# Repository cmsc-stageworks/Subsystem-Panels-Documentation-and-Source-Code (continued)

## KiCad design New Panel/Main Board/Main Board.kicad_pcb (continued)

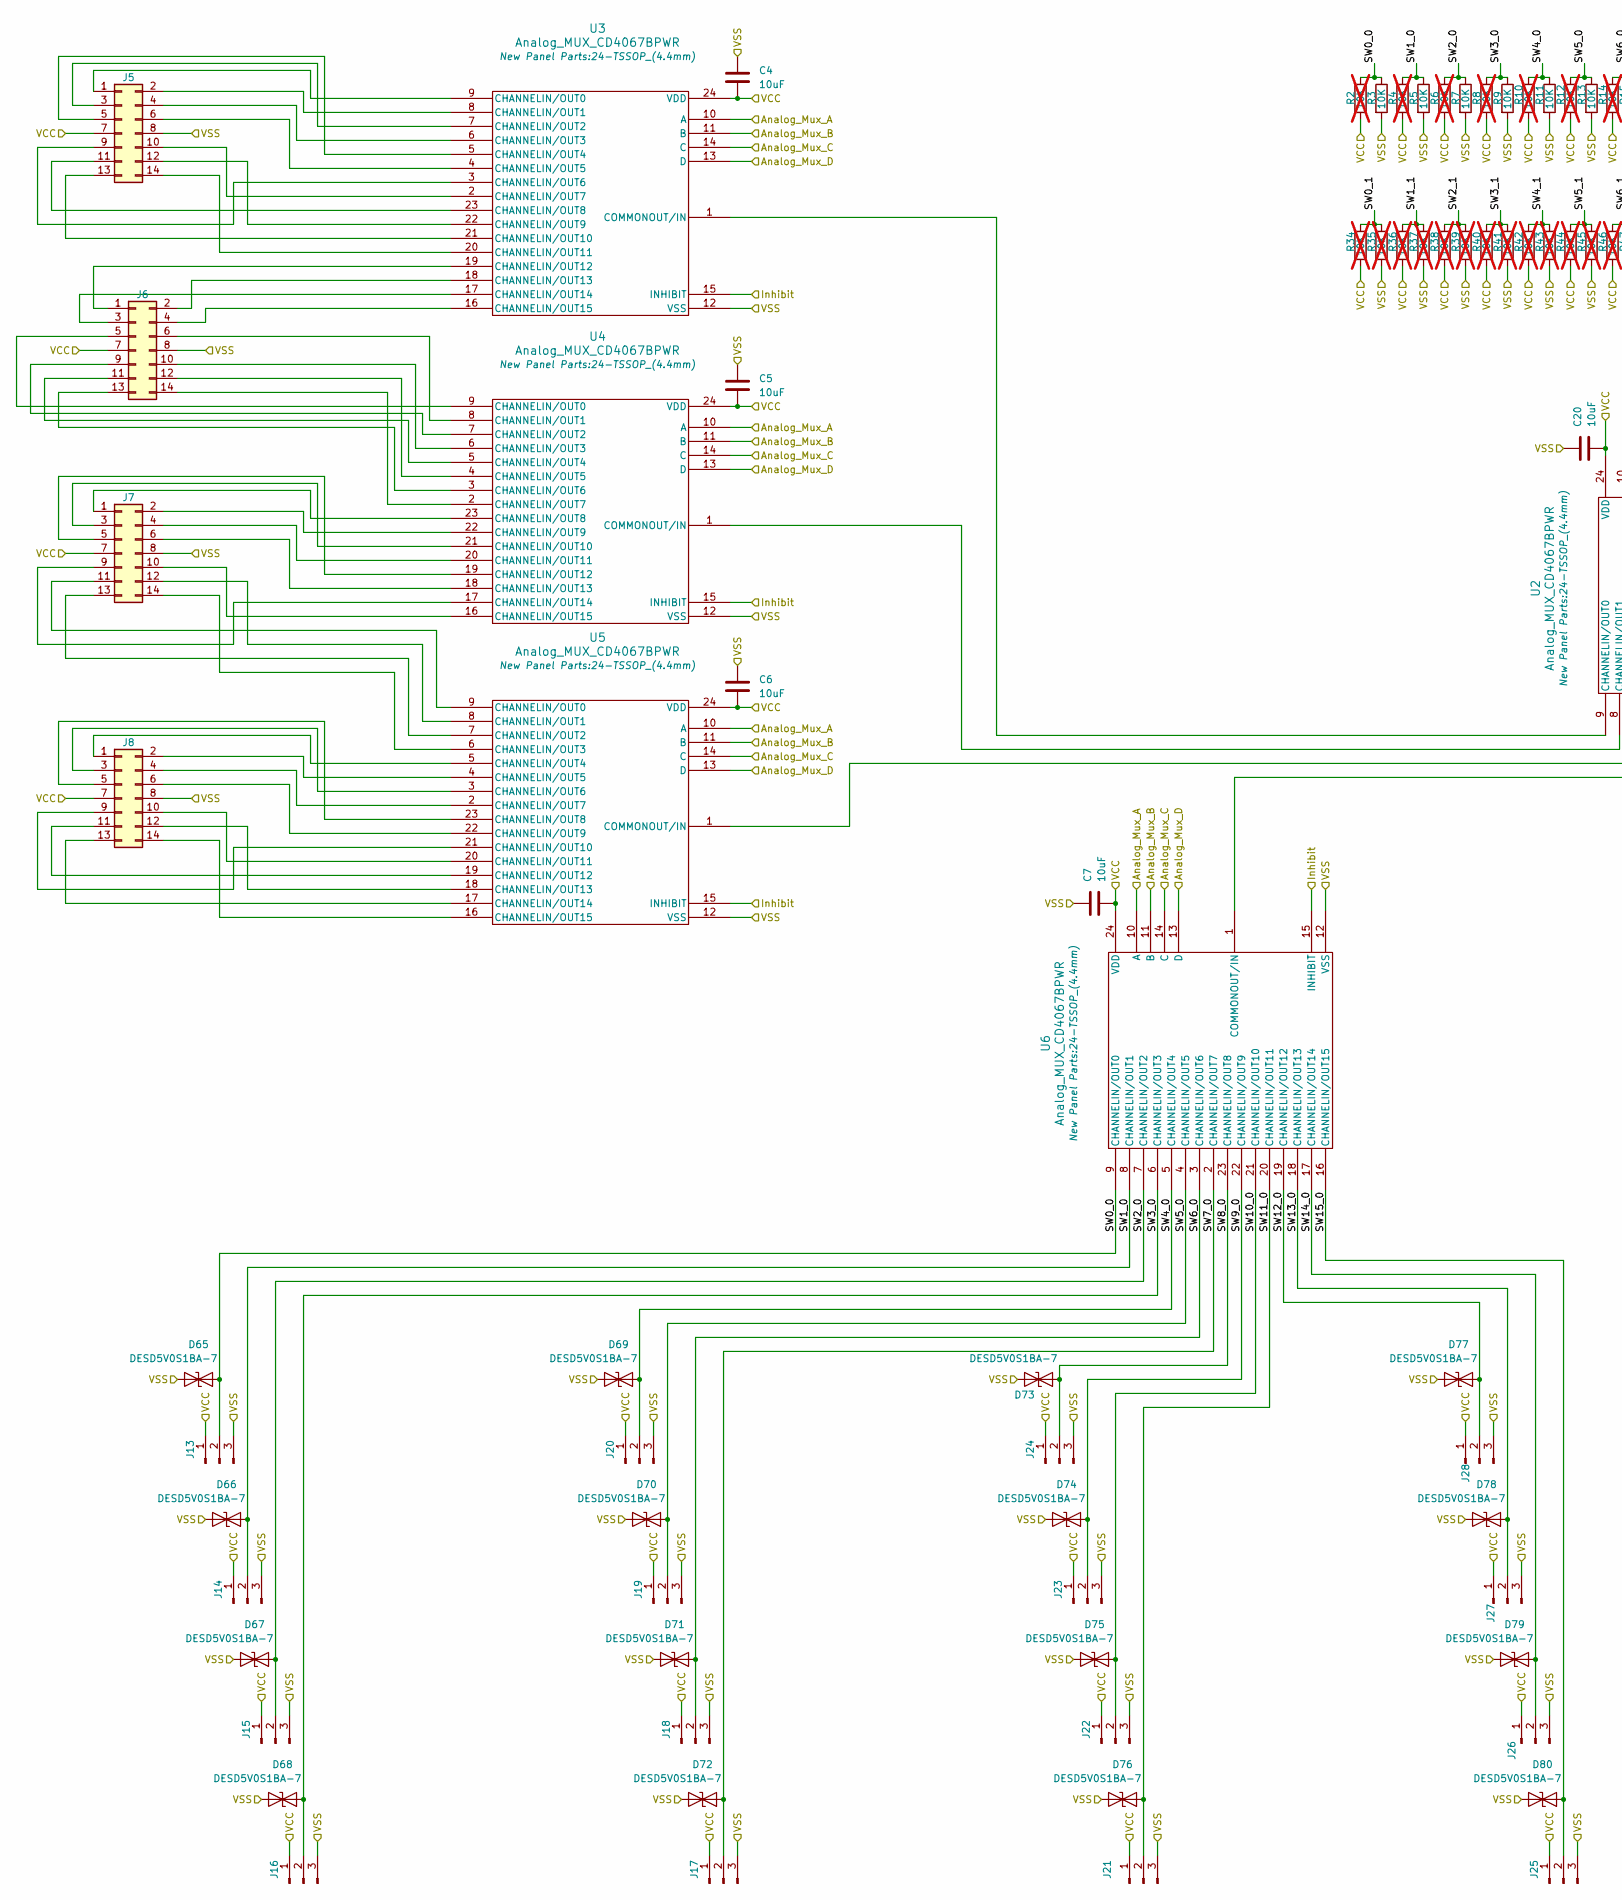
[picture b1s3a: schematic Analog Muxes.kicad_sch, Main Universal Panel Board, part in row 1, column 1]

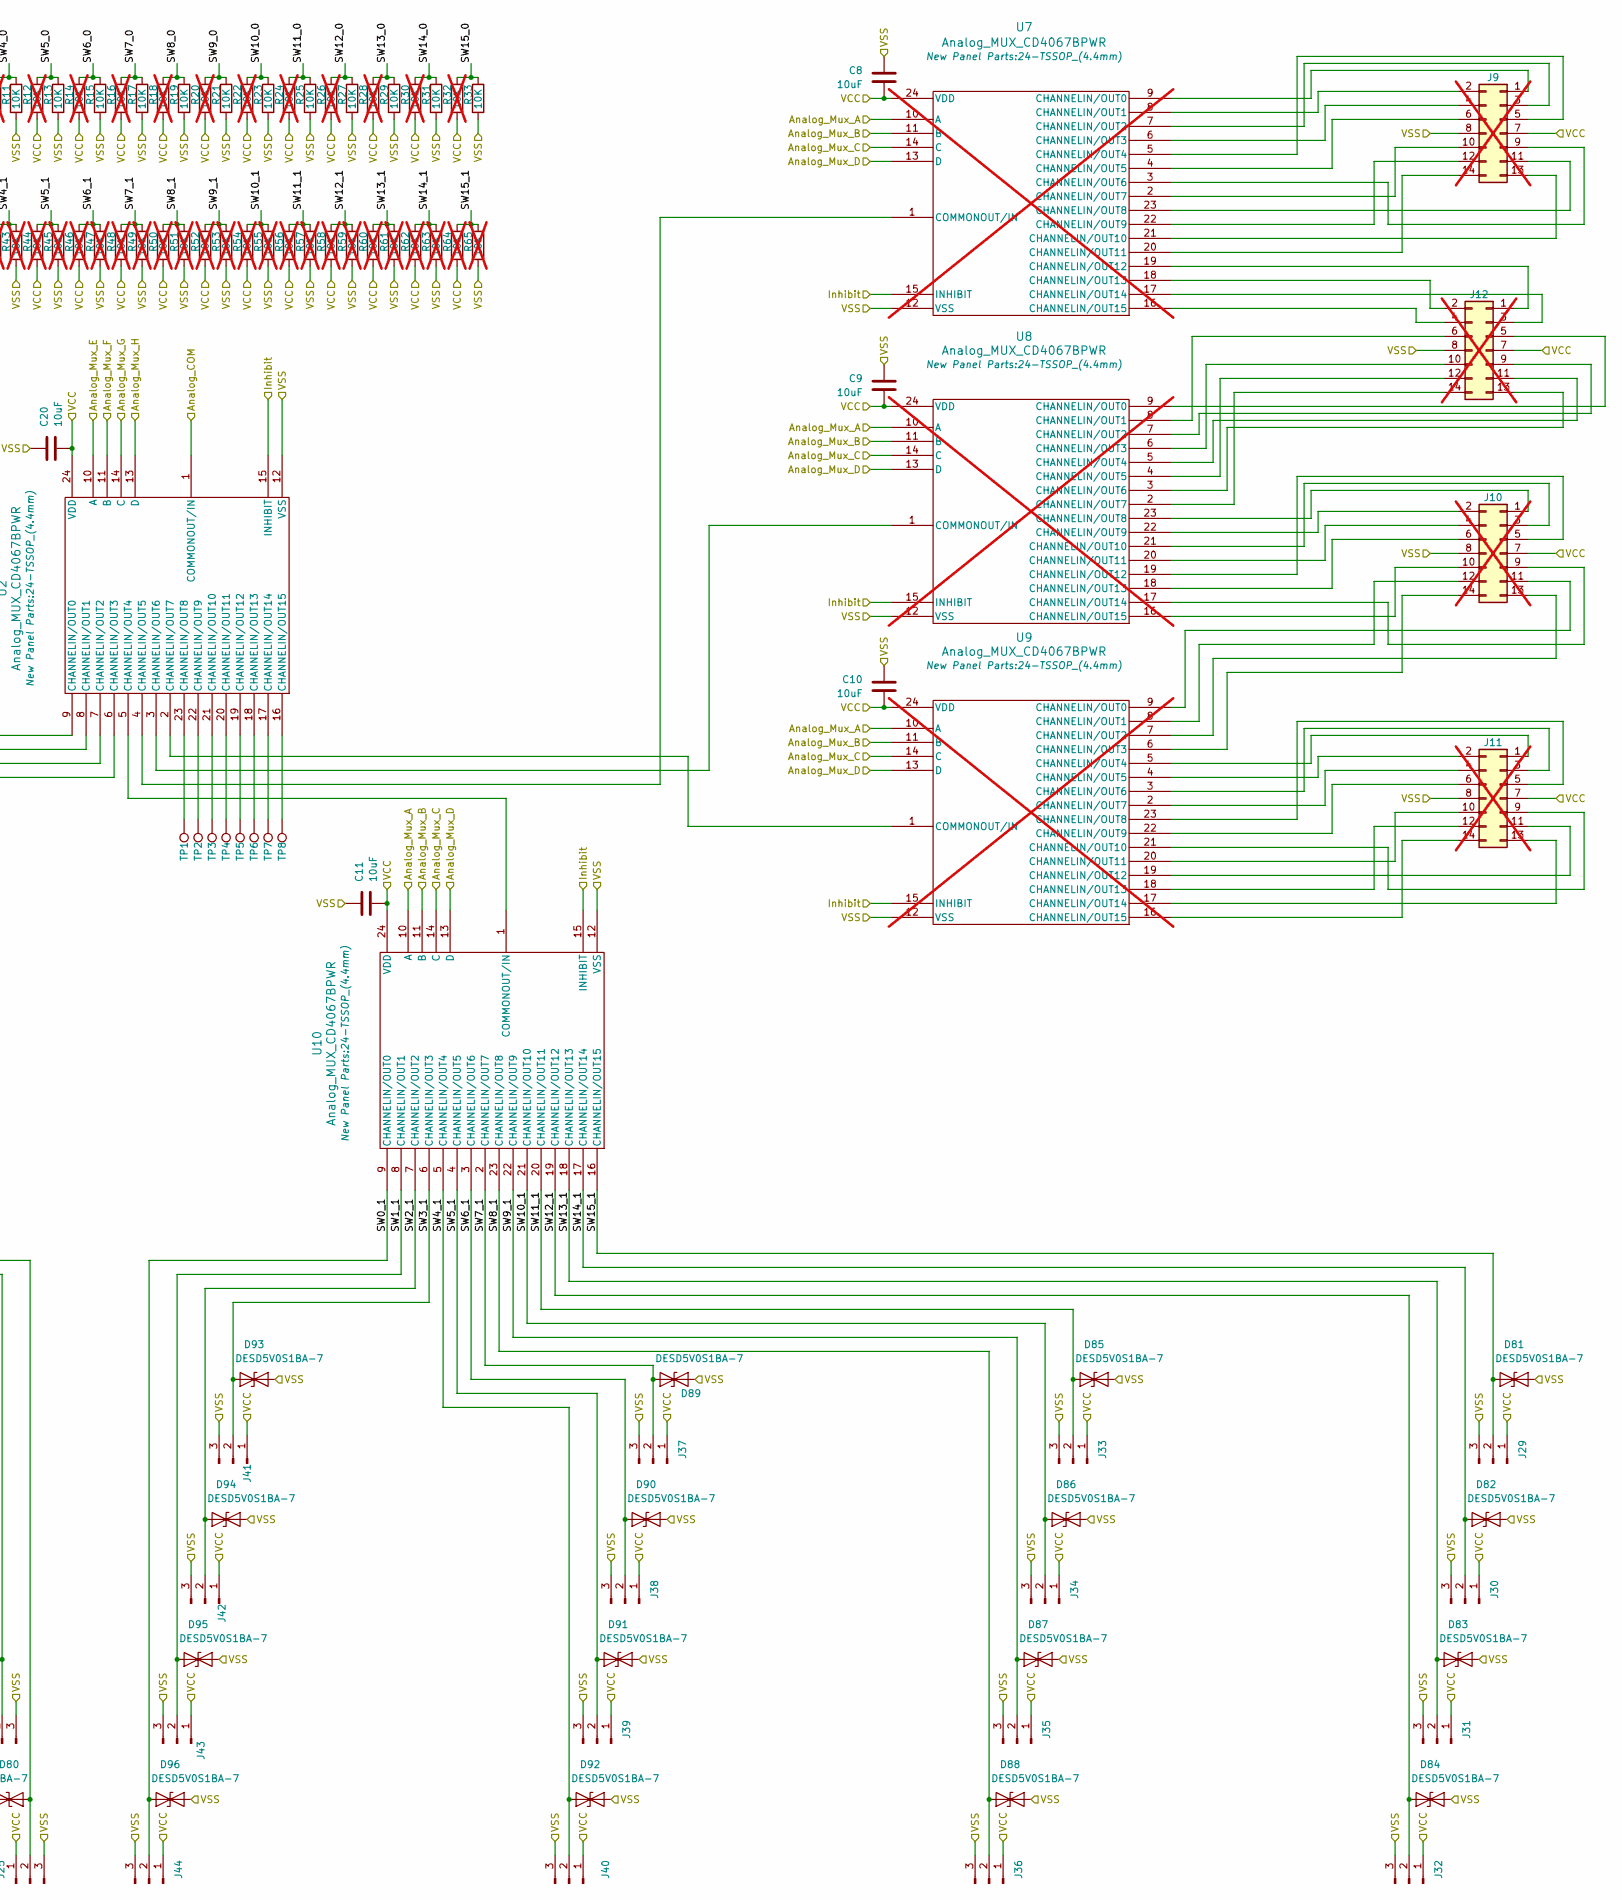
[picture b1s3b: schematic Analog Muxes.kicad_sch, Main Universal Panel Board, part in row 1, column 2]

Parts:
C4, C5, C6, C7, C8, C9, C10, C11, C20: 10uF; C_0603_1608Metric_Pad1.08x0.95mm_HandSolder
D65, D66, D67, D68, D69, D70, D71, D72, D73, D74, D75, D76, D77, D78, D79, D80, D81, D82, D83, D84, D85, D86, D87, D88, D89, D90, D91, D92, D93, D94, D95, D96: DESD5V0S1BA-7; D_SOD-323
J5, J6, J7, J8: Conn_02x07_Odd_Even; IDC-Header_2x07_P2.54mm_Vertical
J9, J10, J11, J12: Conn_02x07_Odd_Even; IDC-Header_2x07_P2.54mm_Vertical; not fitted
J13, J14, J15, J16, J17, J18, J19, J20, J21, J22, J23, J24, J25, J26, J27, J28, J29, J30, J31, J32, J33, J34, J35, J36, J37, J38, J39, J40, J41, J42, J43, J44: Conn_01x03_Pin; JST_PH_B3B-PH-K_1x03_P2.00mm_Vertical
R2, R4, R6, R8, R10, R12, R14, R16, R18, R20, R22, R24, R26, R28, R30, R32, R34, R35, R36, R37, R38, R39, R40, R41, R42, R43, R44, R45, R46, R47, R48, R49, R50, R51, R52, R53, R54, R55, R56, R57, R58, R59, R60, R61, R62, R63, R64, R65: 10K; R_0603_1608Metric; not fitted
R3, R5, R7, R9, R11, R13, R15, R17, R19, R21, R23, R25, R27, R29, R31, R33: 10K; R_0603_1608Metric
TP1, TP2, TP3, TP4, TP5, TP6, TP7, TP8: TestPoint; Pin_D1.0mm_L10.0mm
U2, U3, U4, U5, U6, U10: Analog_MUX_CD4067BPWR; 24-TSSOP_(4.4mm); Manufacturer Part Number CD4067BPWR
U7, U8, U9: Analog_MUX_CD4067BPWR; 24-TSSOP_(4.4mm); Manufacturer Part Number CD4067BPWR; not fitted

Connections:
+3.3V: C4.2, C5.2, C6.2, C7.2, C8.2, C9.2, C10.2, C11.2, C20.2, J5.7, J6.7, J7.7, J8.7, J9.7, J10.7, J11.7, J12.7, J13.1, J14.1, J15.1, J16.1, J17.1, J18.1, J19.1, J20.1, J21.1, J22.1, J23.1, J24.1, J25.1, J26.1, J27.1, J28.1, J29.1, J30.1, J31.1, J32.1, J33.1, J34.1, J35.1, J36.1, J37.1, J38.1, J39.1, J40.1, J41.1, J42.1, J43.1, J44.1, R2.2, R4.2, R6.2, R8.2, R10.2, R12.2, R14.2, R16.2, R18.2, R20.2, R22.2, R24.2, R26.2, R28.2, R30.2, R32.2, R34.2, R36.2, R38.2, R40.2, R42.2, R44.2, R46.2, R48.2, R50.2, R52.2, R54.2, R56.2, R58.2, R60.2, R62.2, R64.2, U2.24 (VDD), U3.24 (VDD), U4.24 (VDD), U5.24 (VDD), U6.24 (VDD), U7.24 (VDD), U8.24 (VDD), U9.24 (VDD), U10.24 (VDD); also elsewhere on the board
/Analog Input Mux/Analog_COM: U2.1 (COMMONOUT/IN); also elsewhere on the board
/Analog Input Mux/Analog_Mux_A: U3.10 (A), U4.10 (A), U5.10 (A), U6.10 (A), U7.10 (A), U8.10 (A), U9.10 (A), U10.10 (A); also elsewhere on the board
/Analog Input Mux/Analog_Mux_B: U3.11 (B), U4.11 (B), U5.11 (B), U6.11 (B), U7.11 (B), U8.11 (B), U9.11 (B), U10.11 (B); also elsewhere on the board
/Analog Input Mux/Analog_Mux_C: U3.14 (C), U4.14 (C), U5.14 (C), U6.14 (C), U7.14 (C), U8.14 (C), U9.14 (C), U10.14 (C); also elsewhere on the board
/Analog Input Mux/Analog_Mux_D: U3.13 (D), U4.13 (D), U5.13 (D), U6.13 (D), U7.13 (D), U8.13 (D), U9.13 (D), U10.13 (D); also elsewhere on the board
/Analog Input Mux/Analog_Mux_E: U2.10 (A); also elsewhere on the board
/Analog Input Mux/Analog_Mux_F: U2.11 (B); also elsewhere on the board
/Analog Input Mux/Analog_Mux_G: U2.14 (C); also elsewhere on the board
/Analog Input Mux/Analog_Mux_H: U2.13 (D); also elsewhere on the board
/Analog Input Mux/Inhibit: U2.15 (INHIBIT), U3.15 (INHIBIT), U4.15 (INHIBIT), U5.15 (INHIBIT), U6.15 (INHIBIT), U7.15 (INHIBIT), U8.15 (INHIBIT), U9.15 (INHIBIT), U10.15 (INHIBIT); also elsewhere on the board
/Analog Input Mux/SW0_0: D65.1 (A1), J13.2, R2.1, R3.1, U6.9 (CHANNELIN/OUT0)
/Analog Input Mux/SW0_1: D96.1 (A1), J44.2, R34.1, R35.1, U10.9 (CHANNELIN/OUT0)
/Analog Input Mux/SW1_0: D66.1 (A1), J14.2, R4.1, R5.1, U6.8 (CHANNELIN/OUT1)
/Analog Input Mux/SW1_1: D95.1 (A1), J43.2, R36.1, R37.1, U10.8 (CHANNELIN/OUT1)
/Analog Input Mux/SW2_0: D67.1 (A1), J15.2, R6.1, R7.1, U6.7 (CHANNELIN/OUT2)
/Analog Input Mux/SW2_1: D94.1 (A1), J42.2, R38.1, R39.1, U10.7 (CHANNELIN/OUT2)
/Analog Input Mux/SW3_0: D68.1 (A1), J16.2, R8.1, R9.1, U6.6 (CHANNELIN/OUT3)
/Analog Input Mux/SW3_1: D93.1 (A1), J41.2, R40.1, R41.1, U10.6 (CHANNELIN/OUT3)
/Analog Input Mux/SW4_0: D69.1 (A1), J20.2, R10.1, R11.1, U6.5 (CHANNELIN/OUT4)
/Analog Input Mux/SW4_1: D92.1 (A1), J40.2, R42.1, R43.1, U10.5 (CHANNELIN/OUT4)
/Analog Input Mux/SW5_0: D70.1 (A1), J19.2, R12.1, R13.1, U6.4 (CHANNELIN/OUT5)
/Analog Input Mux/SW5_1: D91.1 (A1), J39.2, R44.1, R45.1, U10.4 (CHANNELIN/OUT5)
/Analog Input Mux/SW6_0: D71.1 (A1), J18.2, R14.1, R15.1, U6.3 (CHANNELIN/OUT6)
/Analog Input Mux/SW6_1: D90.1 (A1), J38.2, R46.1, R47.1, U10.3 (CHANNELIN/OUT6)
/Analog Input Mux/SW7_0: D72.1 (A1), J17.2, R16.1, R17.1, U6.2 (CHANNELIN/OUT7)
/Analog Input Mux/SW7_1: D89.1 (A1), J37.2, R48.1, R49.1, U10.2 (CHANNELIN/OUT7)
/Analog Input Mux/SW8_0: D73.1 (A1), J24.2, R18.1, R19.1, U6.23 (CHANNELIN/OUT8)
/Analog Input Mux/SW8_1: D88.1 (A1), J36.2, R50.1, R51.1, U10.23 (CHANNELIN/OUT8)
/Analog Input Mux/SW9_0: D74.1 (A1), J23.2, R20.1, R21.1, U6.22 (CHANNELIN/OUT9)
/Analog Input Mux/SW9_1: D87.1 (A1), J35.2, R52.1, R53.1, U10.22 (CHANNELIN/OUT9)
/Analog Input Mux/SW10_0: D75.1 (A1), J22.2, R22.1, R23.1, U6.21 (CHANNELIN/OUT10)
/Analog Input Mux/SW10_1: D86.1 (A1), J34.2, R54.1, R55.1, U10.21 (CHANNELIN/OUT10)
/Analog Input Mux/SW11_0: D76.1 (A1), J21.2, R24.1, R25.1, U6.20 (CHANNELIN/OUT11)
/Analog Input Mux/SW11_1: D85.1 (A1), J33.2, R56.1, R57.1, U10.20 (CHANNELIN/OUT11)
/Analog Input Mux/SW12_0: D77.1 (A1), J28.2, R26.1, R27.1, U6.19 (CHANNELIN/OUT12)
/Analog Input Mux/SW12_1: D84.1 (A1), J32.2, R58.1, R59.1, U10.19 (CHANNELIN/OUT12)
/Analog Input Mux/SW13_0: D78.1 (A1), J27.2, R28.1, R29.1, U6.18 (CHANNELIN/OUT13)
/Analog Input Mux/SW13_1: D83.1 (A1), J31.2, R60.1, R61.1, U10.18 (CHANNELIN/OUT13)
/Analog Input Mux/SW14_0: D79.1 (A1), J26.2, R30.1, R31.1, U6.17 (CHANNELIN/OUT14)
/Analog Input Mux/SW14_1: D82.1 (A1), J30.2, R62.1, R63.1, U10.17 (CHANNELIN/OUT14)
/Analog Input Mux/SW15_0: D80.1 (A1), J25.2, R32.1, R33.1, U6.16 (CHANNELIN/OUT15)
/Analog Input Mux/SW15_1: D81.1 (A1), J29.2, R64.1, R65.1, U10.16 (CHANNELIN/OUT15)
GND: C4.1, C5.1, C6.1, C7.1, C8.1, C9.1, C10.1, C11.1, C20.1, D65.2 (A2), D66.2 (A2), D67.2 (A2), D68.2 (A2), D69.2 (A2), D70.2 (A2), D71.2 (A2), D72.2 (A2), D73.2 (A2), D74.2 (A2), D75.2 (A2), D76.2 (A2), D77.2 (A2), D78.2 (A2), D79.2 (A2), D80.2 (A2), D81.2 (A2), D82.2 (A2), D83.2 (A2), D84.2 (A2), D85.2 (A2), D86.2 (A2), D87.2 (A2), D88.2 (A2), D89.2 (A2), D90.2 (A2), D91.2 (A2), D92.2 (A2), D93.2 (A2), D94.2 (A2), D95.2 (A2), D96.2 (A2), J5.8, J6.8, J7.8, J8.8, J9.8, J10.8, J11.8, J12.8, J13.3, J14.3, J15.3, J16.3, J17.3, J18.3, J19.3, J20.3, J21.3, J22.3, J23.3, J24.3, J25.3, J26.3, J27.3, J28.3, J29.3, J30.3, J31.3, J32.3, J33.3, J34.3, J35.3, J36.3, J37.3, J38.3, J39.3, J40.3, J41.3, J42.3, J43.3, J44.3, R3.2, R5.2, R7.2, R9.2, R11.2, R13.2, R15.2, R17.2, R19.2, R21.2, R23.2, R25.2, R27.2, R29.2, R31.2, R33.2, R35.2, R37.2, R39.2, R41.2, R43.2, R45.2, R47.2, R49.2, R51.2, R53.2, R55.2, R57.2, R59.2, R61.2, R63.2, R65.2, U2.12 (VSS), U3.12 (VSS), U4.12 (VSS), U5.12 (VSS), U6.12 (VSS), U7.12 (VSS), U8.12 (VSS), U9.12 (VSS), U10.12 (VSS); also elsewhere on the board
unnamed: J5.1, U3.9 (CHANNELIN/OUT0)
unnamed: J5.2, U3.8 (CHANNELIN/OUT1)
unnamed: J5.3, U3.7 (CHANNELIN/OUT2)
unnamed: J5.4, U3.6 (CHANNELIN/OUT3)
unnamed: J5.5, U3.5 (CHANNELIN/OUT4)
unnamed: J5.6, U3.4 (CHANNELIN/OUT5)
unnamed: J5.9, U3.3 (CHANNELIN/OUT6)
unnamed: J5.10, U3.2 (CHANNELIN/OUT7)
unnamed: J5.11, U3.23 (CHANNELIN/OUT8)
unnamed: J5.12, U3.22 (CHANNELIN/OUT9)
unnamed: J5.13, U3.21 (CHANNELIN/OUT10)
unnamed: J5.14, U3.20 (CHANNELIN/OUT11)
unnamed: J6.1, U3.19 (CHANNELIN/OUT12)
unnamed: J6.2, U3.18 (CHANNELIN/OUT13)
unnamed: J6.3, U3.17 (CHANNELIN/OUT14)
unnamed: J6.4, U3.16 (CHANNELIN/OUT15)
unnamed: J6.5, U4.9 (CHANNELIN/OUT0)
unnamed: J6.6, U4.8 (CHANNELIN/OUT1)
unnamed: J6.9, U4.7 (CHANNELIN/OUT2)
unnamed: J6.10, U4.6 (CHANNELIN/OUT3)
unnamed: J6.11, U4.5 (CHANNELIN/OUT4)
unnamed: J6.12, U4.4 (CHANNELIN/OUT5)
unnamed: J6.13, U4.3 (CHANNELIN/OUT6)
unnamed: J6.14, U4.2 (CHANNELIN/OUT7)
unnamed: J7.1, U4.23 (CHANNELIN/OUT8)
unnamed: J7.2, U4.22 (CHANNELIN/OUT9)
unnamed: J7.3, U4.21 (CHANNELIN/OUT10)
unnamed: J7.4, U4.20 (CHANNELIN/OUT11)
unnamed: J7.5, U4.19 (CHANNELIN/OUT12)
unnamed: J7.6, U4.18 (CHANNELIN/OUT13)
unnamed: J7.9, U4.17 (CHANNELIN/OUT14)
unnamed: J7.10, U4.16 (CHANNELIN/OUT15)
unnamed: J7.11, U5.9 (CHANNELIN/OUT0)
unnamed: J7.12, U5.8 (CHANNELIN/OUT1)
unnamed: J7.13, U5.7 (CHANNELIN/OUT2)
unnamed: J7.14, U5.6 (CHANNELIN/OUT3)
unnamed: J8.1, U5.5 (CHANNELIN/OUT4)
unnamed: J8.2, U5.4 (CHANNELIN/OUT5)
unnamed: J8.3, U5.3 (CHANNELIN/OUT6)
unnamed: J8.4, U5.2 (CHANNELIN/OUT7)
unnamed: J8.5, U5.23 (CHANNELIN/OUT8)
unnamed: J8.6, U5.22 (CHANNELIN/OUT9)
unnamed: J8.9, U5.21 (CHANNELIN/OUT10)
unnamed: J8.10, U5.20 (CHANNELIN/OUT11)
unnamed: J8.11, U5.19 (CHANNELIN/OUT12)
unnamed: J8.12, U5.18 (CHANNELIN/OUT13)
unnamed: J8.13, U5.17 (CHANNELIN/OUT14)
unnamed: J8.14, U5.16 (CHANNELIN/OUT15)
unnamed: J9.1, U7.9 (CHANNELIN/OUT0)
unnamed: J9.2, U7.8 (CHANNELIN/OUT1)
unnamed: J9.3, U7.7 (CHANNELIN/OUT2)
unnamed: J9.4, U7.6 (CHANNELIN/OUT3)
unnamed: J9.5, U7.5 (CHANNELIN/OUT4)
unnamed: J9.6, U7.4 (CHANNELIN/OUT5)
unnamed: J9.9, U7.3 (CHANNELIN/OUT6)
unnamed: J9.10, U7.2 (CHANNELIN/OUT7)
unnamed: J9.11, U7.23 (CHANNELIN/OUT8)
unnamed: J9.12, U7.22 (CHANNELIN/OUT9)
unnamed: J9.13, U7.21 (CHANNELIN/OUT10)
unnamed: J9.14, U7.20 (CHANNELIN/OUT11)
unnamed: J10.1, U8.23 (CHANNELIN/OUT8)
unnamed: J10.2, U8.22 (CHANNELIN/OUT9)
unnamed: J10.3, U8.21 (CHANNELIN/OUT10)
unnamed: J10.4, U8.20 (CHANNELIN/OUT11)
unnamed: J10.5, U8.19 (CHANNELIN/OUT12)
unnamed: J10.6, U8.18 (CHANNELIN/OUT13)
unnamed: J10.9, U8.17 (CHANNELIN/OUT14)
unnamed: J10.10, U8.16 (CHANNELIN/OUT15)
unnamed: J10.11, U9.9 (CHANNELIN/OUT0)
unnamed: J10.12, U9.8 (CHANNELIN/OUT1)
unnamed: J10.13, U9.7 (CHANNELIN/OUT2)
unnamed: J10.14, U9.6 (CHANNELIN/OUT3)
unnamed: J11.1, U9.5 (CHANNELIN/OUT4)
unnamed: J11.2, U9.4 (CHANNELIN/OUT5)
unnamed: J11.3, U9.3 (CHANNELIN/OUT6)
unnamed: J11.4, U9.2 (CHANNELIN/OUT7)
unnamed: J11.5, U9.23 (CHANNELIN/OUT8)
unnamed: J11.6, U9.22 (CHANNELIN/OUT9)
unnamed: J11.9, U9.21 (CHANNELIN/OUT10)
unnamed: J11.10, U9.20 (CHANNELIN/OUT11)
unnamed: J11.11, U9.19 (CHANNELIN/OUT12)
unnamed: J11.12, U9.18 (CHANNELIN/OUT13)
unnamed: J11.13, U9.17 (CHANNELIN/OUT14)
unnamed: J11.14, U9.16 (CHANNELIN/OUT15)
unnamed: J12.1, U7.19 (CHANNELIN/OUT12)
unnamed: J12.2, U7.18 (CHANNELIN/OUT13)
unnamed: J12.3, U7.17 (CHANNELIN/OUT14)
unnamed: J12.4, U7.16 (CHANNELIN/OUT15)
unnamed: J12.5, U8.9 (CHANNELIN/OUT0)
unnamed: J12.6, U8.8 (CHANNELIN/OUT1)
unnamed: J12.9, U8.7 (CHANNELIN/OUT2)
unnamed: J12.10, U8.6 (CHANNELIN/OUT3)
unnamed: J12.11, U8.5 (CHANNELIN/OUT4)
unnamed: J12.12, U8.4 (CHANNELIN/OUT5)
unnamed: J12.13, U8.3 (CHANNELIN/OUT6)
unnamed: J12.14, U8.2 (CHANNELIN/OUT7)
unnamed: U2.9 (CHANNELIN/OUT0), U3.1 (COMMONOUT/IN)
unnamed: U2.8 (CHANNELIN/OUT1), U4.1 (COMMONOUT/IN)
unnamed: U2.7 (CHANNELIN/OUT2), U5.1 (COMMONOUT/IN)
unnamed: U2.6 (CHANNELIN/OUT3), U6.1 (COMMONOUT/IN)
unnamed: U2.4 (CHANNELIN/OUT5), U7.1 (COMMONOUT/IN)
unnamed: U2.3 (CHANNELIN/OUT6), U8.1 (COMMONOUT/IN)
unnamed: U2.2 (CHANNELIN/OUT7), U9.1 (COMMONOUT/IN)
unnamed: TP1.1, U2.23 (CHANNELIN/OUT8)
unnamed: TP2.1, U2.22 (CHANNELIN/OUT9)
unnamed: TP3.1, U2.21 (CHANNELIN/OUT10)
unnamed: TP4.1, U2.20 (CHANNELIN/OUT11)
unnamed: TP5.1, U2.19 (CHANNELIN/OUT12)
unnamed: TP6.1, U2.18 (CHANNELIN/OUT13)
unnamed: TP7.1, U2.17 (CHANNELIN/OUT14)
unnamed: TP8.1, U2.16 (CHANNELIN/OUT15)
unnamed: U2.5 (CHANNELIN/OUT4), U10.1 (COMMONOUT/IN)

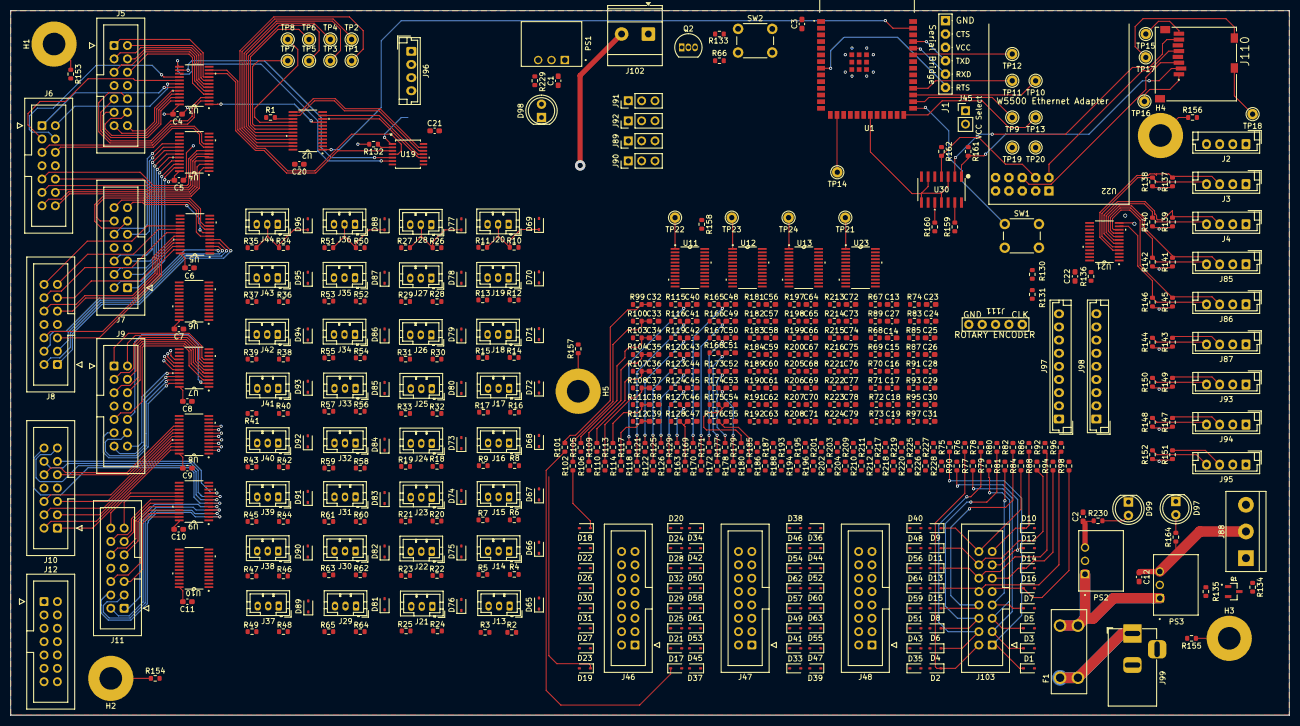
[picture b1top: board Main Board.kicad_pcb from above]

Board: 4 copper layers, 243.2 x 134.0 mm, 530 parts (0 on the bottom side), 358 nets.

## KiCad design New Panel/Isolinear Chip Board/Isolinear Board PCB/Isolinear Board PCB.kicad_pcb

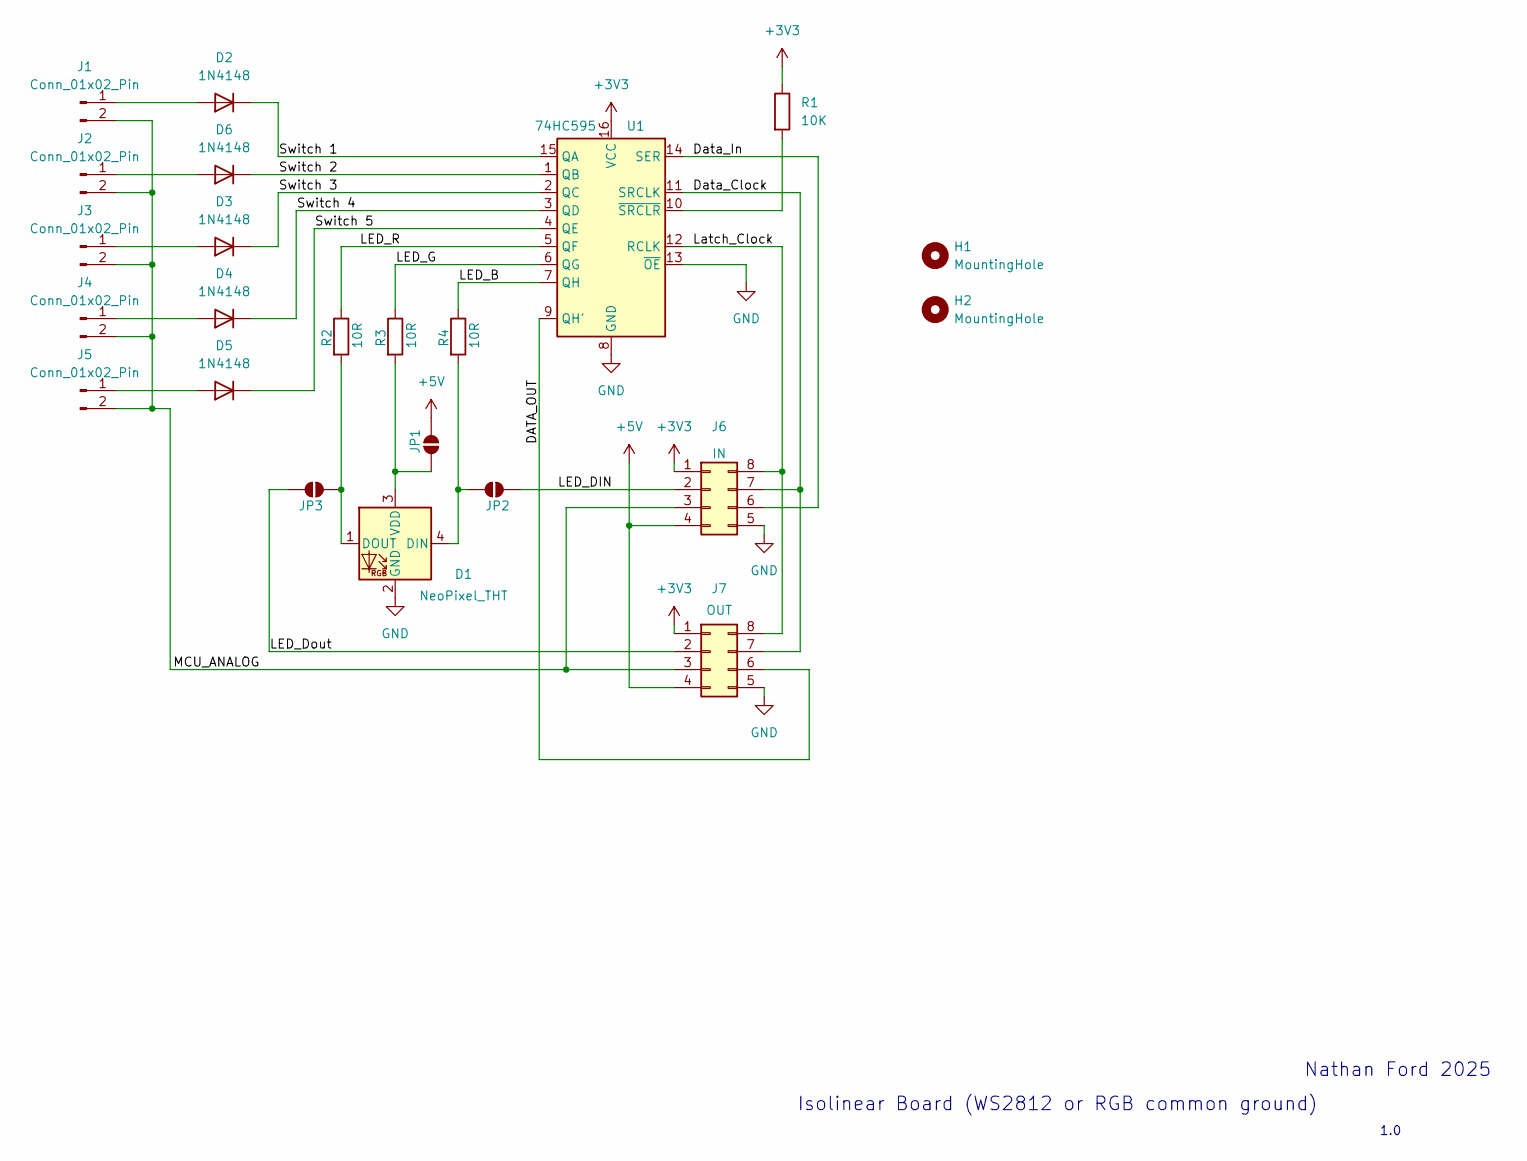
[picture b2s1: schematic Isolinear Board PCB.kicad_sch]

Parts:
D1: NeoPixel_THT; LED_D5.0mm-4_RGB_Staggered_Pins
D2, D3, D4, D5, D6: 1N4148; D_DO-35_SOD27_P7.62mm_Horizontal
H1: MountingHole; MountingHole_3.2mm_M3
H2: MountingHole; MountingHole_2.1mm
J1, J2, J3, J4, J5: Conn_01x02_Pin; JST_XH_B02B-XH-A_02x2.50mm_Straight
J6: IN; IDC-Header_2x04_P2.54mm_Vertical
J7: OUT; IDC-Header_2x04_P2.54mm_Vertical
JP1, JP2, JP3: SolderJumper_2_Open; SolderJumper-2_P1.3mm_Open_TrianglePad1.0x1.5mm
R1: 10K; R_Axial_DIN0207_L6.3mm_D2.5mm_P7.62mm_Horizontal
R2, R3, R4: 10R; R_Axial_DIN0207_L6.3mm_D2.5mm_P7.62mm_Horizontal
U1: 74HC595; DIP-16_W7.62mm_LongPads

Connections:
+3V3: J6.1, J7.1, R1.1, U1.16 (VCC)
+5V: J6.4, J7.4, JP1.2 (B)
/DATA_OUT: J7.6, U1.9 (QH')
/Data_Clock: J6.7, J7.7, U1.11 (SRCLK)
/Data_In: J6.6, U1.14 (SER)
/LED_B: R4.1, U1.7 (QH)
/LED_DIN: J6.2, JP2.2 (B)
/LED_Dout: J7.2, JP3.2 (B)
/LED_G: R3.1, U1.6 (QG)
/LED_R: R2.1, U1.5 (QF)
/Latch_Clock: J6.8, J7.8, U1.12 (RCLK)
/MCU_ANALOG: J1.2, J2.2, J3.2, J4.2, J5.2, J6.3, J7.3
/Switch 1: D2.1 (K), U1.15 (QA)
/Switch 2: D6.1 (K), U1.1 (QB)
/Switch 3: D3.1 (K), U1.2 (QC)
/Switch 4: D4.1 (K), U1.3 (QD)
/Switch 5: D5.1 (K), U1.4 (QE)
GND: D1.2 (GND), J6.5, J7.5, U1.8 (GND), U1.13 (~OE)
unnamed: D1.4 (DIN), JP2.1 (A), R4.2
unnamed: D1.1 (DOUT), JP3.1 (A), R2.2
unnamed: D1.3 (VDD), JP1.1 (A), R3.2
unnamed: D2.2 (A), J1.1
unnamed: D3.2 (A), J3.1
unnamed: D4.2 (A), J4.1
unnamed: D5.2 (A), J5.1
unnamed: D6.2 (A), J2.1
unnamed: R1.2, U1.10 (~SRCLR)

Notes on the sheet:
Isolinear Board (WS2812 or RGB common ground)
1.0
Nathan Ford 2025

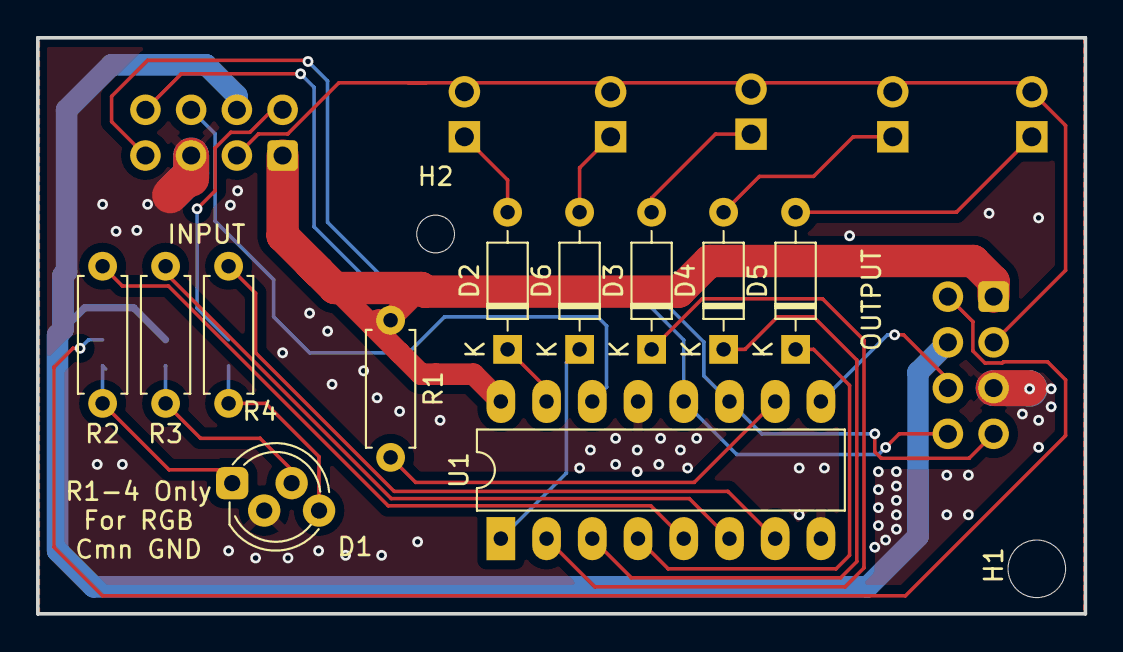
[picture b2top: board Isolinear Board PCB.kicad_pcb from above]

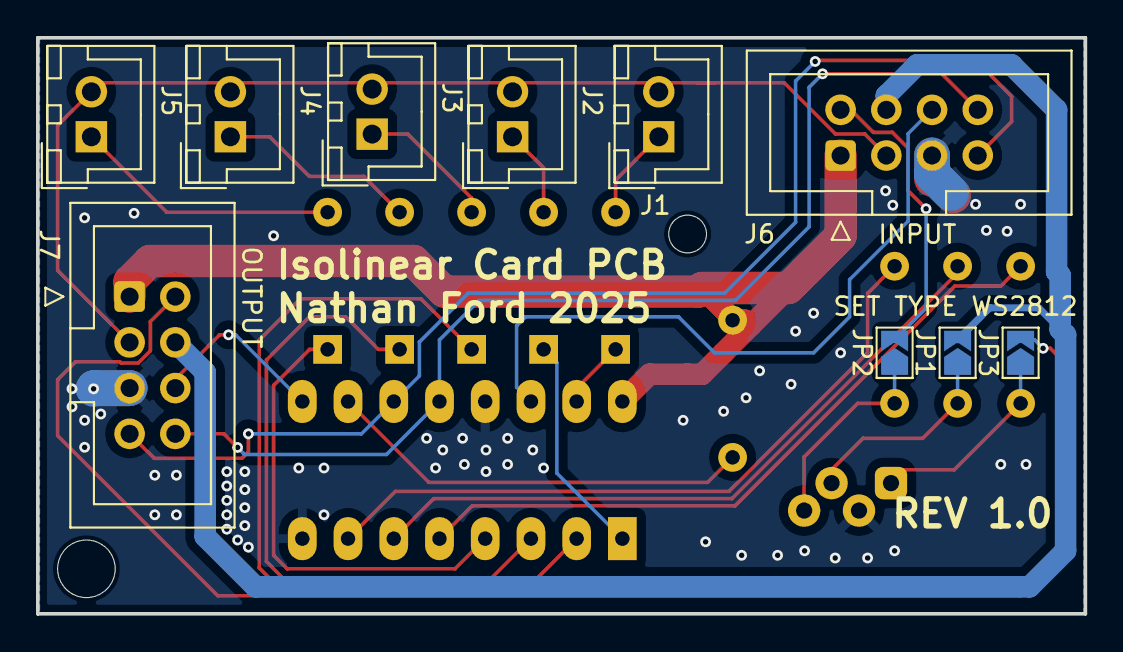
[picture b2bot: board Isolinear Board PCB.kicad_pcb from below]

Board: 2 copper layers, 58.2 x 32.0 mm, 23 parts (10 on the bottom side), 27 nets.

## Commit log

2022-03-24 Added Documentation
    Enjoy!
2024-09-19 Moved PCB Directory to the repo
    I've been working on these and I just needed to add them
2024-09-19 Cleaned up main pcb folder
2024-09-19 Removed useless files
2024-09-19 Created a new folder for the new 4th iteration of the PCB
    I need to adjust the SPI Header to allow for the reset signal to be sent, along with this I will just route an extra pin from the mega to the touch SPI Interface, just in case someone wants to take a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
2024-09-19 Started Work on SPI Board Rework
    need to change the size of the board for the 2.8" screen and also change the connector out, as well as use the raw parts for the bi-directional logic level converter.
2024-09-20 Updates to V3 of the SPI Breakout Board
2024-09-20 Finished SPI Breakout Board V3
2024-09-20 Added Resistor Values
2024-09-20 Fixed some labels on the silkscreen
2024-09-20 Minor visual glitch fix on silkscreen
2024-09-20 Fixed drill hole positions
2024-10-03 Fixed the headers to include reset for the SPI interface and expansion for future touch control if wanted
2024-10-09 various fabrication outputs
2024-10-16 added neopixel stabalization
    added capacitor slot and resistor slot, both are optional but can be added to increase stability.
2024-10-17 Added Parts List and files for button board
2024-10-17 opened a file and github detects a change of some kind
2024-10-21 added a piece I forgot to the parts list
2025-01-18 more work
2025-02-02 updated some files, added panel code
2025-03-02 started work on updated ethernet controller
2025-03-02 Moved Compiling enviornments to VS Code
2025-03-16 updated subsystem code
2025-05-10 Updated Subsystem code
    - now has webpage for setting MQTT address
    - communication via MQTT to central server
    - panel name is now stored on SD card
2025-05-20 Updated PCBs
    - Updated PCBs for the subsystem main
    - Started work on an idea for a new panel (on my own time)
2025-08-07 Work on new main pcb
2025-08-13 adjusted schematic and started PCB Work
2025-08-16 Continued PCB Layout
2025-09-20 moved main board to new repo
2025-09-20 Moved New Panel to its own repo
